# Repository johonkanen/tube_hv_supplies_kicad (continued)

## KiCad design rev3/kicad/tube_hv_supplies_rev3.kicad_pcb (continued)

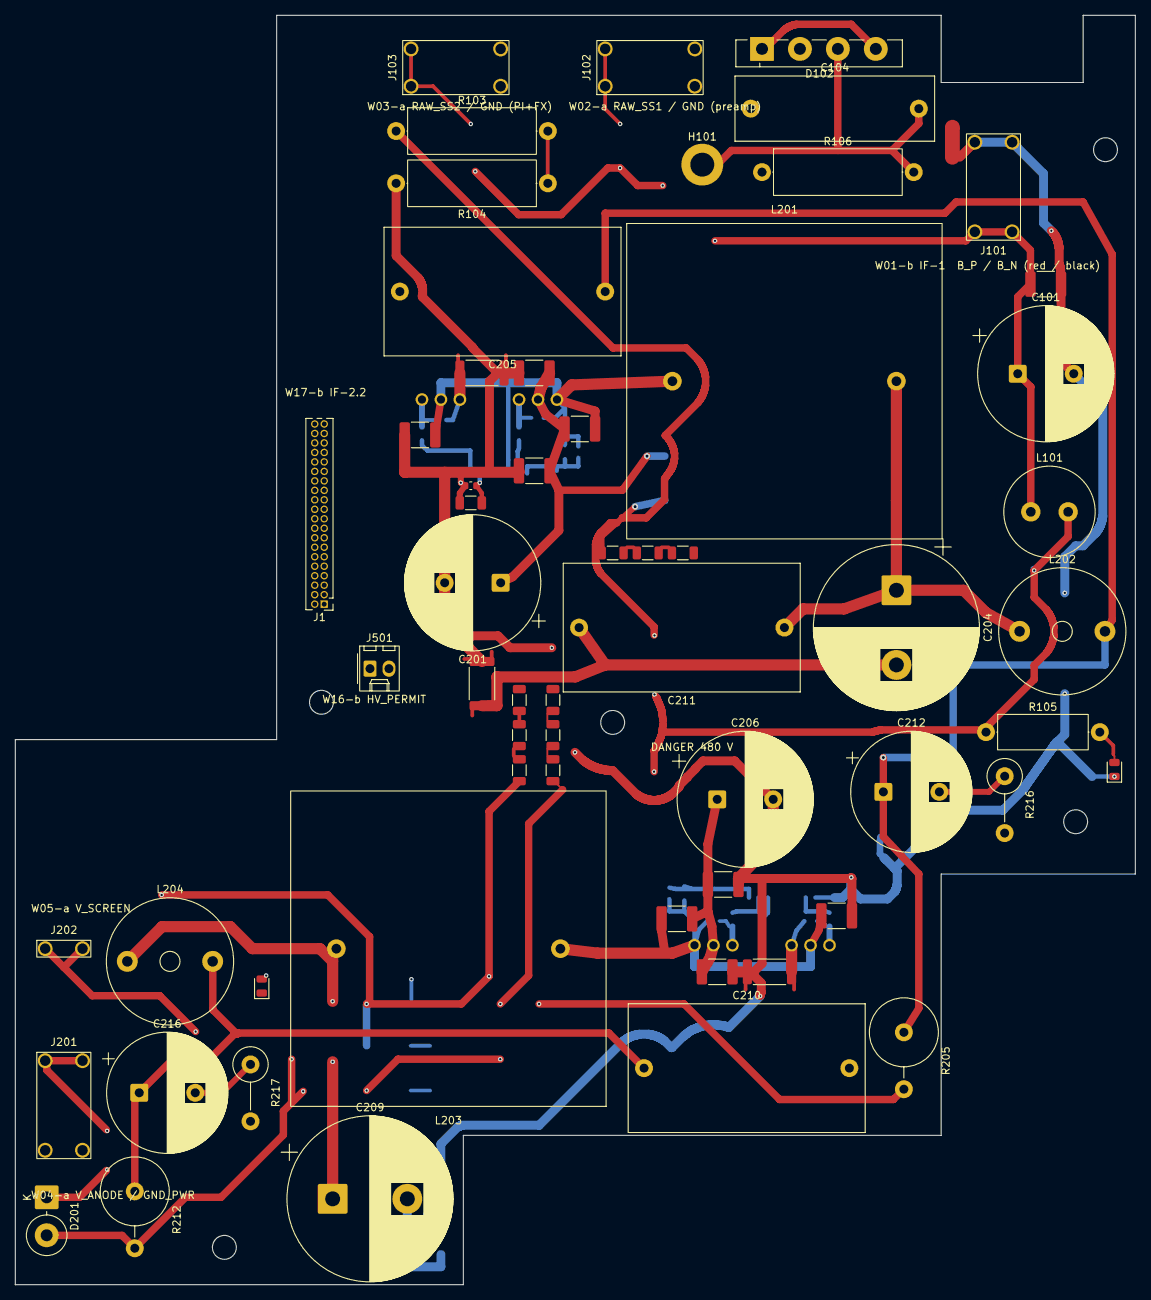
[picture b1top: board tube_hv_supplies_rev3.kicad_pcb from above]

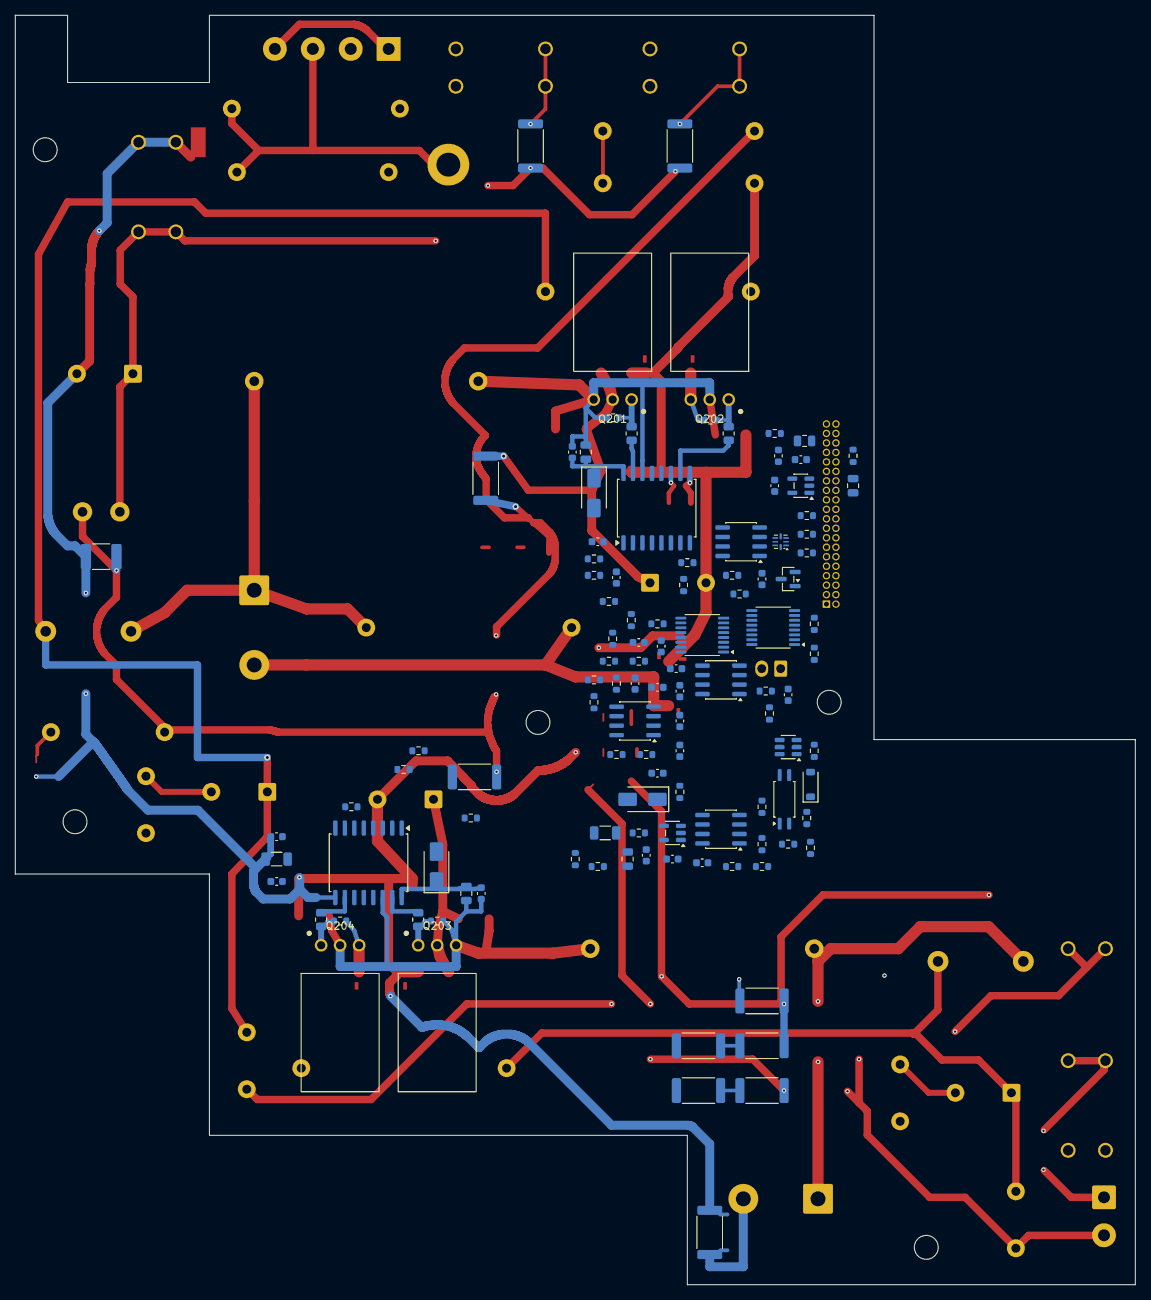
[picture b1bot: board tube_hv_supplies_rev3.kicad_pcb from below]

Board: 4 copper layers, 150.0 x 170.0 mm, 187 parts (115 on the bottom side), 108 nets.

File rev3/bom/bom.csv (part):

refs,qty,value,footprint,candidate_mpn,dnp,placeholder,note
C101 C201 C206,3,47u/500V 105C,Capacitor_THT:CP_Radial_D18.0mm_P7.50mm,,,,"radial D18, ripple rating at 70 C to check"
C102 C202 C207,3,100n/630V X7R 1812,Capacitor_SMD:C_1812_4532Metric,,,,
C103 C203 C208,3,1n/1kV C0G 1812,Capacitor_SMD:C_1812_4532Metric,,,,
C104,1,100n Y2 300VAC,Capacitor_THT:C_Rect_L26.5mm_W8.5mm_P22.50mm_MKS4,TDK B32023A3104M,,,"Y2 film, P22.5 (body width to check against the TDK drawing)"
C204 C209,2,100u/500V 105C 5000h snap-in,Capacitor_THT:CP_Radial_D22.0mm_P10.00mm_SnapIn,"Vishay MAL215919101E3 (PUL-SI, 22 x 40)",,,"TCM ripple 0.2-0.84 A rms at 40-150 kHz (sim/r2_filter.py); about 0.8 A at 120 Hz / 105 C rated, x1.4 at >= 10 kHz, more at 80 C: to confirm on the Vishay datasheet; alternative Rubycon 500VXT100MEFCSN22X25"
C205 C210 C211,3,4.7u/630V MKP DC-link,Capacitor_THT:C_Rect_L31.5mm_W17.0mm_P27.50mm_MKS4,TDK B32674D6475K,,,"C1 film, returned through the I_C shunt with the electrolytic: 0.2-0.76 A rms at 40-150 kHz (sim/r2); ripple rating to confirm on the TDK datasheet (DC-link series, ESR 7.5 mohm); C2 of the second stage (L2-C2 8.9 kHz); ESR 7.5 mohm; ripple current small (residue mV)"
C212 C216,2,22u/500V 105C,Capacitor_THT:CP_Radial_D16.0mm_P7.50mm,,,,damping leg of the second stage (with its ESR about 1.5 ohm in all); ripple small
C213 C217,2,"220p/1kV C0G 1812 (snubber, high side)",Capacitor_SMD:C_1812_4532Metric,,,,lossless ZVS snubber across the IGBT (sim/r1); at the device pins
C214 C218,2,"220p/1kV C0G 1812 (snubber, low side)",Capacitor_SMD:C_1812_4532Metric,,,,"lossless ZVS snubber across the IGBT, returned to PGND beside the shunt (keeps its charging current off the reading)"
C301 C303 C305 C308 C310 C312 C402 C404 C406 C408 C409 C410 C411 C414 C504 C505,16,100n,Capacitor_SMD:C_0603_1608Metric,,,,
C302 C309,2,1u/25V X7R,Capacitor_SMD:C_0805_2012Metric,,,,
C304 C311,2,10u/25V X7R,Capacitor_SMD:C_1206_3216Metric,,,,
C401 C403,2,100p C0G (tau 1.2 us),Capacitor_SMD:C_0603_1608Metric,,,,
C405,1,1n (tau 15 us),Capacitor_SMD:C_0603_1608Metric,,,,
C407 C413,2,1u X7R,Capacitor_SMD:C_0603_1608Metric,,,,
C412,1,"680p C0G (charge bucket, 22 ns)",Capacitor_SMD:C_0603_1608Metric,,,,
C415 C501,2,10u,Capacitor_SMD:C_0805_2012Metric,,,,
C416,1,10u X7R,Capacitor_SMD:C_0805_2012Metric,,,,
C502,1,10u/25V,Capacitor_SMD:C_1206_3216Metric,,,,
C503,1,10n,Capacitor_SMD:C_0603_1608Metric,,,,
D101,1,"red, 0.4 mA (HV PRESENT)",LED_SMD:LED_0805_2012Metric,,,,
D102,1,"GBU8J (8 A 600 V, + and - joined: anti-parallel pair)",Diode_THT:Diode_Bridge_Vishay_GBU,GBU8J,,,
D201,1,1N5408 (clamp: V_SCREEN <= V_ANODE + 0.7 V),Diode_THT:D_DO-201AD_P5.08mm_Vertical_CathodeUp,1N5408,,,
D202,1,"red, 0.4 mA (V_ANODE PRESENT)",LED_SMD:LED_0805_2012Metric,,,,
D301 D302,2,ES1J (600 V ultrafast),Diode_SMD:D_SMA,ES1J,,,
D501,1,SMAJ24CA,Diode_SMD:D_SMA,SMAJ24CA,,,
D502,1,1N4148W (reverse),Diode_SMD:D_SOD-123,1N4148W,,,
FB401,1,600R@100MHz 0603,Inductor_SMD:L_0603_1608Metric,,,,with C: the reference's input filter (LDO-derived 3V3 from the link)
H101,1,"CHASSIS standoff, plated (fault / RF network)",MountingHole:MountingHole_3.2mm_M3_DIN965_Pad,,,,new plate hole next to J101 (mechanical/floorplan.md)
H102 H103 H104 H105 H106,5,"M3, non-plated (no chassis contact)",MountingHole:MountingHole_3.2mm_M3,,,,"standoffs (fourth pass, mechanical/floorplan_chosen.md): (600.0, 98.0) (671.0, 48.0) (667.0, 138.0) (553.0, 195.0) (566.0, 122.0)"
J1,1,"CONTROL 40-pin IF-2.3 (W17-b, isolated on the control board)",Connector_PinHeader_1.27mm:PinHeader_2x20_P1.27mm_Vertical,Samtec SHF-120-01-L-D-TH,,,1.27 mm 2x20 shrouded THT header; the unused HV-to-card pads tied low
J101,2,"HV IN: B_P / B_N (W01-b, 4.8 mm tabs)",tube_hv_supplies_rev3:Blade_Tab_4.8mm_2x_P12mm,,,,"4.8 mm PCB blade tab(s), fully insulated receptacle; qty = tabs"
J102,2,RAW OUT 1 to preamp J501 (W02-a): RAW_SS1 / GND_PRE1,tube_hv_supplies_rev3:Blade_Tab_4.8mm_2x_P12mm,,,,"4.8 mm PCB blade tab(s), fully insulated receptacle; qty = tabs"
J103,2,RAW OUT 2 to PI + FX (W03-a): RAW_SS2 / GND_PRE2,tube_hv_supplies_rev3:Blade_Tab_4.8mm_2x_P12mm,,,,"4.8 mm PCB blade tab(s), fully insulated receptacle; qty = tabs"
J201,2,"V_ANODE / GND_PWR (W04-a, 4.8 mm tabs)",tube_hv_supplies_rev3:Blade_Tab_4.8mm_2x_P12mm,,,,"4.8 mm PCB blade tab(s), fully insulated receptacle; qty = tabs"
J202,1,"V_SCREEN (W05-a, 4.8 mm tab)",tube_hv_supplies_rev3:Blade_Tab_4.8mm_1x,,,,"4.8 mm PCB blade tab(s), fully insulated receptacle; qty = tabs"
J501,1,"HV_PERMIT +/- (W16-b, Lock-2.54, twisted pair)",Connector_Molex:Molex_KK-254_AE-6410-02A_1x02_P2.54mm_Vertical,Molex 22-27-2021,,,
L101,1,33uH 2A,Inductor_THT:L_Radial_D12.0mm_P5.00mm_Fastron_11P,,,,"33 uH, >= 2 A, radial D12"
L201,1,"220uH ETD39 N97, 50t litz 0.8mm2, gap ~1.8mm (Isat >= 10A, DCR ~0.1R hot)",tube_hv_supplies_rev3:L_ETD39_2pin_custom,TDK B66363G0000X197 (N97) core set + ETD39 bobbin,,,custom-wound; litz 0.1 mm strands; gap split or winding kept 3 mm from the gap (fringing); 600 V winding-core insulation; pin positions to the chosen bobbin
L202 L204,2,68uH >= 2A,Inductor_THT:L_Radial_D16.8mm_P11.43mm_Vishay_IHB-1,Vishay IHB-1 68 uH (current rating to confirm >= 2 A),,,"second stage: carries the DC output current and the audio current, almost no ripple"
L203,1,"470uH ETD39 N97, 64t litz 0.5mm2, gap ~1.4mm (Isat >= 6A, DCR ~0.2R hot)",tube_hv_supplies_rev3:L_ETD39_2pin_custom,TDK B66363G0000X197 (N97) core set + ETD39 bobbin,,,custom-wound; litz 0.1 mm strands; gap split or winding kept 3 mm from the gap (fringing); 600 V winding-core insulation; pin positions to the chosen bobbin
NT101,1,STAR POINT (power star),NetTie:NetTie-2_SMD_Pad2.0mm,,,,
NT401,1,Kelvin tap IC1 (at the shunt),NetTie:NetTie-2_SMD_Pad0.5mm,,,,
NT402 NT404 NT406 NT408,4,Kelvin tap PGND (at the shunt),NetTie:NetTie-2_SMD_Pad0.5mm,,,,
NT403,1,Kelvin tap IS1 (at the shunt),NetTie:NetTie-2_SMD_Pad0.5mm,,,,
NT405,1,Kelvin tap IC2 (at the shunt),NetTie:NetTie-2_SMD_Pad0.5mm,,,,
NT407,1,Kelvin tap IS2 (at the shunt),NetTie:NetTie-2_SMD_Pad0.5mm,,,,
NT501,1,GND to PGND at the shunts (Kelvin),NetTie:NetTie-2_SMD_Pad0.5mm,,,,
Q201 Q202 Q203 Q204,4,IKP08N65F5,tube_hv_supplies_rev3:TO-220-3_Horizontal_TabUp_Bar,IKP08N65F5XKSA1,,,"lies on the chassis plate: 6 mm aluminium bar, 1.5 mm Al2O3 washer, PEEK shoulder bush, M3 countersunk from the plate's top with a nut on the tab (fitted before the board); leads bent down 90 deg about 5 mm into the board (STATUS fourth pass). Collector tab live: raw rail (high side); lies on the chassis plate: 6 mm aluminium bar, 1.5 mm Al2O3 washer, PEEK shoulder bush, M3 countersunk from the plate's top with a nut on the tab (fitted before the board); leads bent down 90 deg about 5 mm into the board (STATUS fourth pass). Collector tab live: switch node (low side)"
R101 R102,2,0R jumper 2512 (link),Resistor_SMD:R_2512_6332Metric,,,,"link (interfaces.md 4.2), plate side; the fusible-resistor option of the 0617 footprint is dropped (board area, fourth pass)"
R103 R104,2,75k 2W MOX,Resistor_THT:R_Axial_DIN0617_L17.0mm_D6.0mm_P20.32mm_Horizontal,,,,0.62 W each at 430 V
R105,1,1M 1W HV (VR37 class),Resistor_THT:R_Axial_DIN0414_L11.9mm_D4.5mm_P15.24mm_Horizontal,,,,
R106,1,100 2W,Resistor_THT:R_Axial_DIN0617_L17.0mm_D6.0mm_P20.32mm_Horizontal,,,,
R201 R208,2,0R jumper 2512 (bridge input link),Resistor_SMD:R_2512_6332Metric,,,,proposal N7: no fuse (PSU short-circuit protection + 3.0 A trips); plate side (fourth pass)
R202 R203 R209 R210,4,50m 1W 2512 metal strip (Kelvin),Resistor_SMD:R_2512_6332Metric,Vishay WSL2512R0500FEA,,,metal element: M20 pulses up to 220 A / 0.29 J in 0.2 ms on the I_C shunt (pulse rating to confirm)
R205,1,"1.0 5W fusible, pulse (ULW5)",Resistor_THT:R_Axial_DIN0918_L18.0mm_D9.0mm_P7.62mm_Vertical,TT Welwyn ULW5-1R0J (ordering suffix to confirm),,,"M20: a hard short or external arc puts 5.8-6.7 J into it in 0.2 ms; ULW5 short-pulse capacity ~19 J (1R0) / ~13 J (2R2), 500 V isolation (ULW2: 2.5 J, 250 V)"
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
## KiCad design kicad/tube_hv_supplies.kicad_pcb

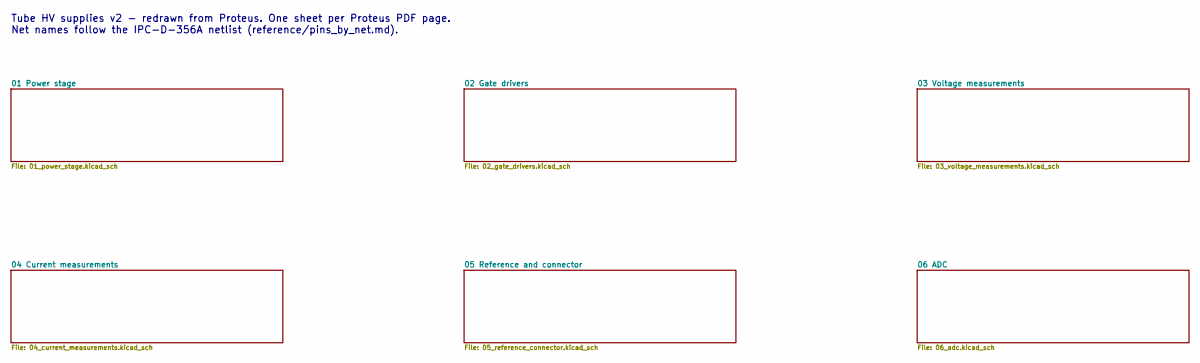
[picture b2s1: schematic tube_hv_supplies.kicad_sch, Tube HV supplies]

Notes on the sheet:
Tube HV supplies v2 - redrawn from Proteus. One sheet per Proteus PDF page. Net names follow the IPC-D-356A netlist (reference/pins_by_net.md).

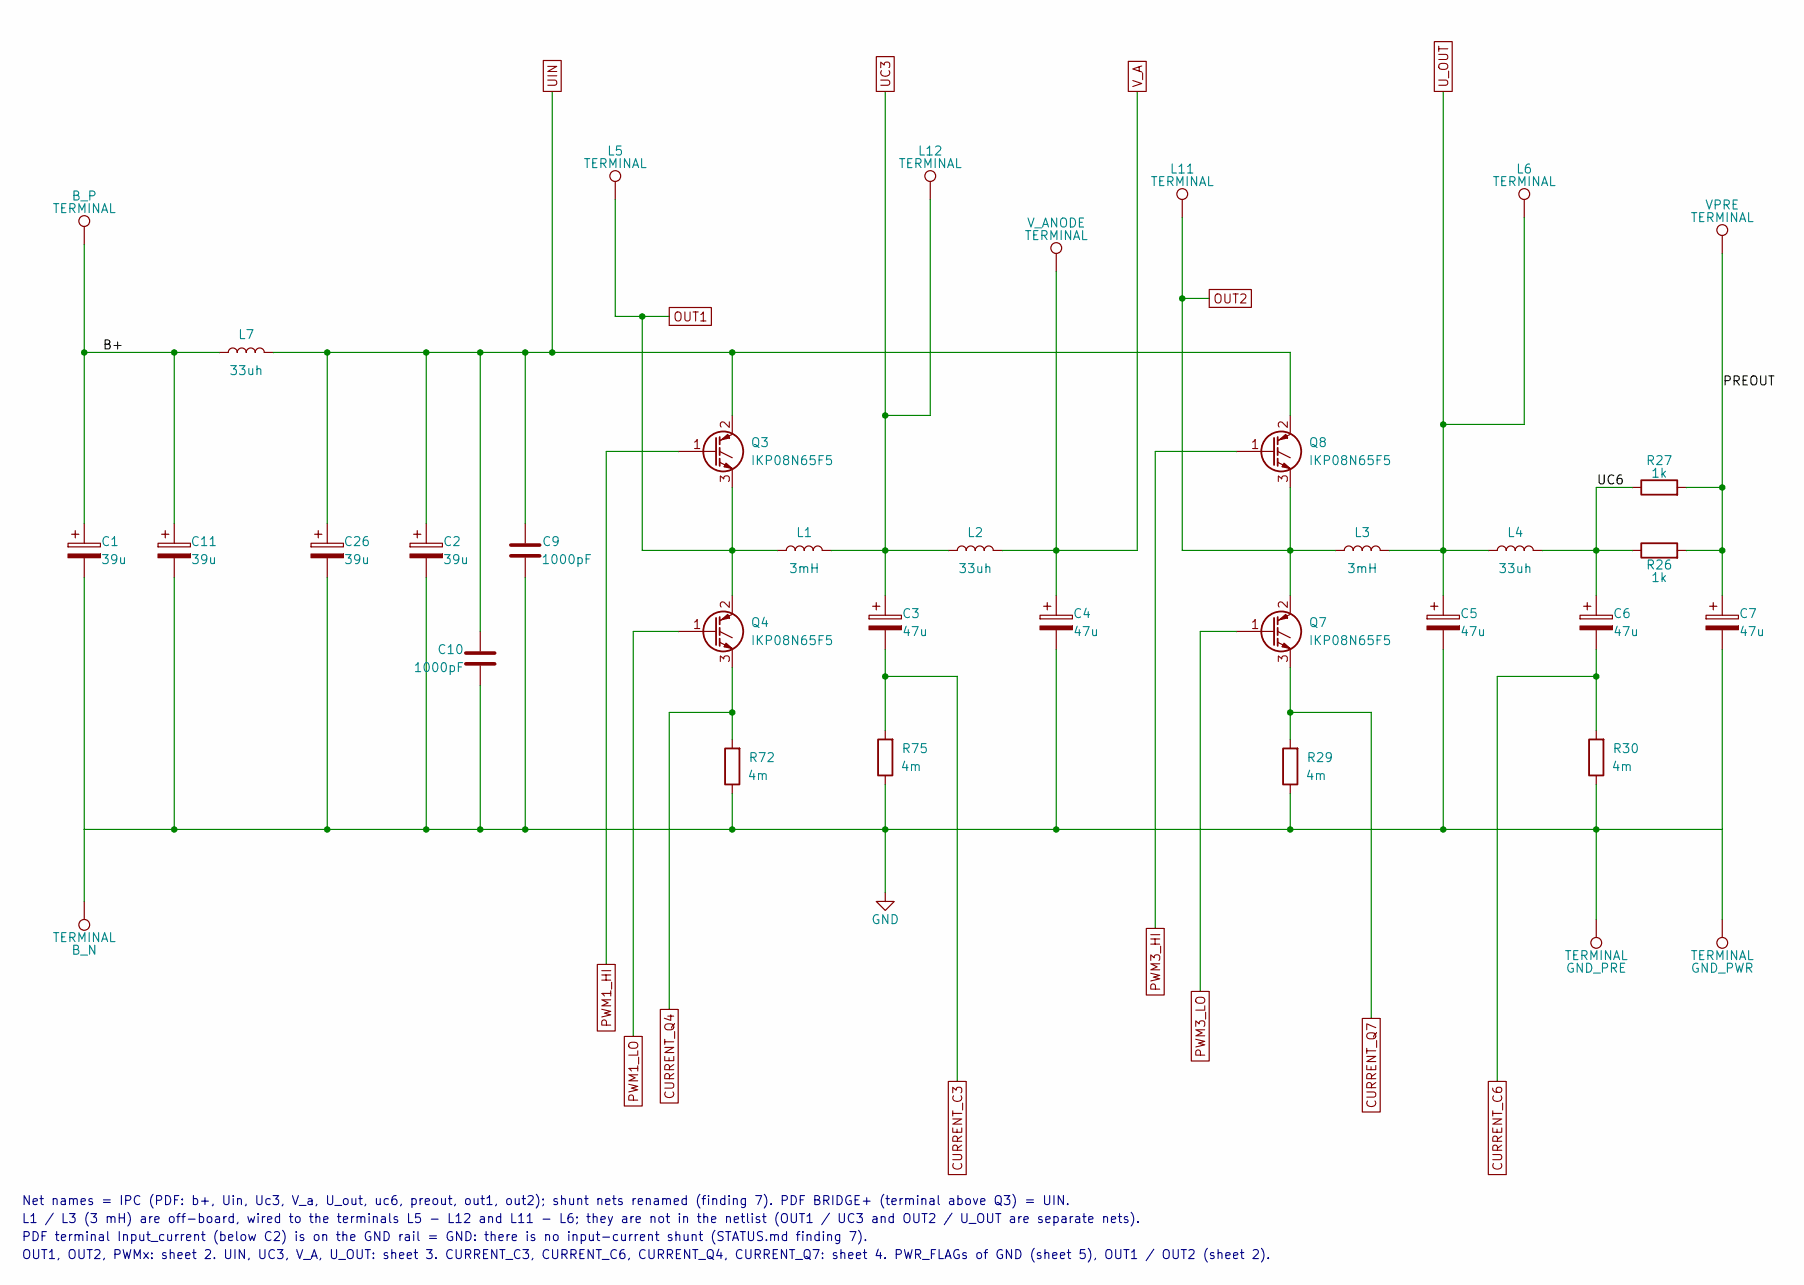
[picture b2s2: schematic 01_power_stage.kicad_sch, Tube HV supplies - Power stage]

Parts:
B_N: TERMINAL; Terminal_2x1_P5.00mm_D2.0mm_Drill1.4mm
B_P: TERMINAL; Terminal_2x1_P5.00mm_D2.0mm_Drill1.4mm
C1, C2, C11, C26: 39u; CP_Radial_D10.0mm_P5.00mm
C3, C4, C5, C6, C7: 47u; CP_Radial_D10.0mm_P5.00mm
C9, C10: 1000pF; C_2220_5750Metric_Pad1.97x5.40mm_HandSolder
GND_PRE: TERMINAL; Terminal_2x1_P5.00mm_D2.0mm_Drill1.4mm
GND_PWR: TERMINAL; Terminal_2x1_P5.00mm_D2.0mm_Drill1.4mm
L1, L3: 3mH
L2, L4, L7: 33uh; L_Bourns_SRP1038C_10.0x10.0mm_Proteus
L5, L6, L11, L12: TERMINAL; Terminal_1x1_D2.54mm_Drill1.524mm
Q3, Q4, Q7, Q8: IKP08N65F5; TO-220-3_Vertical_ProteusPads
R26, R27: 1k; R_1206_3216Metric_Pad1.30x1.75mm_HandSolder
R29, R30, R72, R75: 4m; R_0508_1220Metric_KRL2012
VPRE: TERMINAL; Terminal_2x1_P5.00mm_D2.0mm_Drill1.4mm
V_ANODE: TERMINAL; Terminal_2x1_P5.00mm_D2.0mm_Drill1.4mm

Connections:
/01 Power stage/B+: B_P.1, C1.1, C11.1, L7.1
/01 Power stage/PREOUT: C7.1, R26.2, R27.2, VPRE.1
/01 Power stage/UC6: C6.1, L4.2, R26.1, R27.1
CURRENT_C3: C3.2, R75.2; also elsewhere on the board
CURRENT_C6: C6.2, R30.2; also elsewhere on the board
CURRENT_Q4: Q4.3 (E), R72.2; also elsewhere on the board
CURRENT_Q7: Q7.3 (E), R29.2; also elsewhere on the board
GND: B_N.1, C1.2, C2.2, C4.2, C5.2, C7.2, C9.2, C10.2, C11.2, C26.2, GND_PRE.1, GND_PWR.1, R29.1, R30.1, R72.1, R75.1; also elsewhere on the board
OUT1: L1.1, L5.1, Q3.3 (E), Q4.2 (C); also elsewhere on the board
OUT2: L3.1, L11.1, Q7.2 (C), Q8.3 (E); also elsewhere on the board
PWM1_HI: Q3.1 (G); also elsewhere on the board
PWM1_LO: Q4.1 (G); also elsewhere on the board
PWM3_HI: Q8.1 (G); also elsewhere on the board
PWM3_LO: Q7.1 (G); also elsewhere on the board
UC3: C3.1, L1.2, L2.1, L12.1; also elsewhere on the board
UIN: C2.1, C9.1, C10.1, C26.1, L7.2, Q3.2 (C), Q8.2 (C); also elsewhere on the board
U_OUT: C5.1, L3.2, L4.1, L6.1; also elsewhere on the board
V_A: C4.1, L2.2, V_ANODE.1; also elsewhere on the board

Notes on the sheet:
Net names = IPC (PDF: b+, Uin, Uc3, V_a, U_out, uc6, preout, out1, out2); shunt nets renamed (finding 7). PDF BRIDGE+ (terminal above Q3) = UIN.
L1 / L3 (3 mH) are off-board, wired to the terminals L5 - L12 and L11 - L6; they are not in the netlist (OUT1 / UC3 and OUT2 / U_OUT are separate nets).
PDF terminal Input_current (below C2) is on the GND rail = GND: there is no input-current shunt (STATUS.md finding 7).
OUT1, OUT2, PWMx: sheet 2. UIN, UC3, V_A, U_OUT: sheet 3. CURRENT_C3, CURRENT_C6, CURRENT_Q4, CURRENT_Q7: sheet 4. PWR_FLAGs of GND (sheet 5), OUT1 / OUT2 (sheet 2).

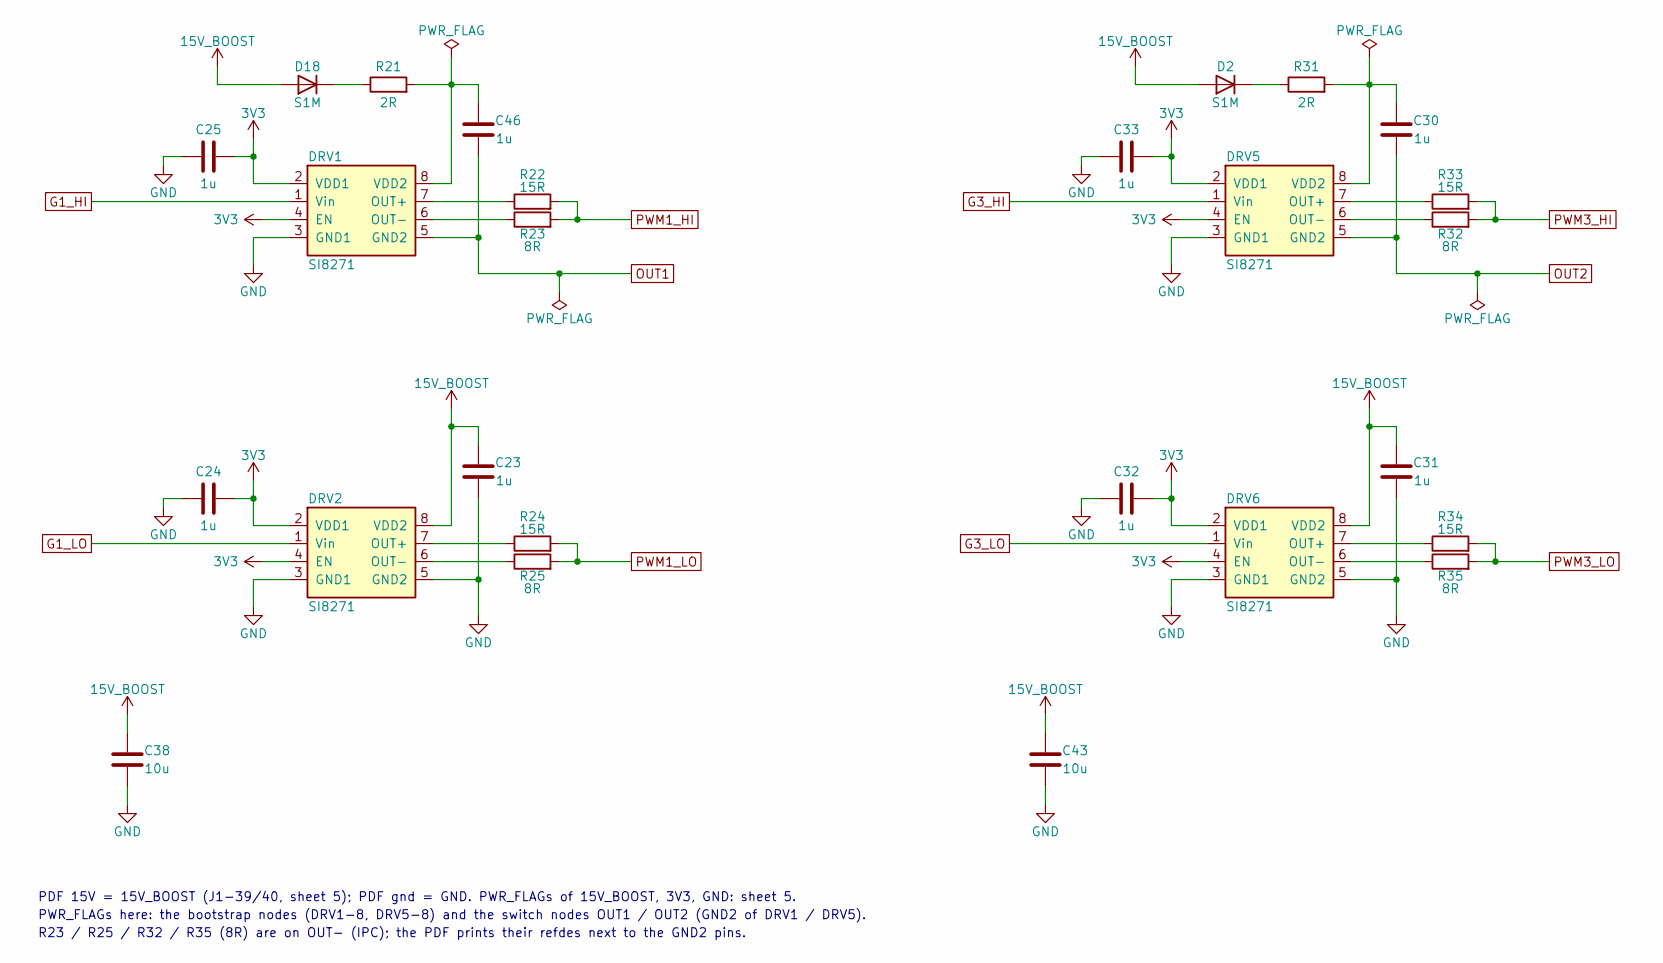
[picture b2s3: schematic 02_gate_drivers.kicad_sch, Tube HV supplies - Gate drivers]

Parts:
C23, C30, C31, C46: 1u; C_1206_3216Metric_Pad1.33x1.80mm_HandSolder
C24, C25, C32, C33: 1u; C_0603_1608Metric_Pad1.08x0.95mm_HandSolder
C38, C43: 10u; C_1206_3216Metric_Pad1.33x1.80mm_HandSolder
D2, D18: S1M; D_SMA_AC
DRV1, DRV2: SI8271; SOIC-8_3.9x4.9mm_P1.27mm_Proteus
DRV5, DRV6: SI8271; SOIC-8_3.9x4.9mm_P1.27mm_Proteus_ProteusPads
R21, R31: 2R; R_1206_3216Metric
R22, R24, R33, R34: 15R; R_1206_3216Metric_Pad1.30x1.75mm_HandSolder
R23, R25, R32, R35: 8R; R_1206_3216Metric_Pad1.30x1.75mm_HandSolder

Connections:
3V3: C24.2, C25.2, C32.2, C33.2, DRV1.2 (VDD1), DRV1.4 (EN), DRV2.2 (VDD1), DRV2.4 (EN), DRV5.2 (VDD1), DRV5.4 (EN), DRV6.2 (VDD1), DRV6.4 (EN); also elsewhere on the board
15V_BOOST: C23.1, C31.1, C38.1, C43.1, D2.A, D18.A, DRV2.8 (VDD2), DRV6.8 (VDD2); also elsewhere on the board
G1_HI: DRV1.1 (Vin); also elsewhere on the board
G1_LO: DRV2.1 (Vin); also elsewhere on the board
G3_HI: DRV5.1 (Vin); also elsewhere on the board
G3_LO: DRV6.1 (Vin); also elsewhere on the board
GND: C23.2, C24.1, C25.1, C31.2, C32.1, C33.1, C38.2, C43.2, DRV1.3 (GND1), DRV2.3 (GND1), DRV2.5 (GND2), DRV5.3 (GND1), DRV6.3 (GND1), DRV6.5 (GND2); also elsewhere on the board
unnamed: D2.C (K), R31.1
unnamed: D18.C (K), R21.1
unnamed: DRV1.7 (OUT+), R22.1
unnamed: DRV1.6 (OUT-), R23.1
unnamed: C46.2, DRV1.8 (VDD2), R21.2
unnamed: DRV2.7 (OUT+), R24.1
unnamed: DRV2.6 (OUT-), R25.1
unnamed: DRV5.7 (OUT+), R33.1
unnamed: DRV5.6 (OUT-), R32.1
unnamed: C30.2, DRV5.8 (VDD2), R31.2
unnamed: DRV6.7 (OUT+), R34.1
unnamed: DRV6.6 (OUT-), R35.1
OUT1: C46.1, DRV1.5 (GND2); also elsewhere on the board
OUT2: C30.1, DRV5.5 (GND2); also elsewhere on the board
PWM1_HI: R22.2, R23.2; also elsewhere on the board
PWM1_LO: R24.2, R25.2; also elsewhere on the board
PWM3_HI: R32.2, R33.2; also elsewhere on the board
PWM3_LO: R34.2, R35.2; also elsewhere on the board

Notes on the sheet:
PDF 15V = 15V_BOOST (J1-39/40, sheet 5); PDF gnd = GND. PWR_FLAGs of 15V_BOOST, 3V3, GND: sheet 5.
PWR_FLAGs here: the bootstrap nodes (DRV1-8, DRV5-8) and the switch nodes OUT1 / OUT2 (GND2 of DRV1 / DRV5).
R23 / R25 / R32 / R35 (8R) are on OUT- (IPC); the PDF prints their refdes next to the GND2 pins.

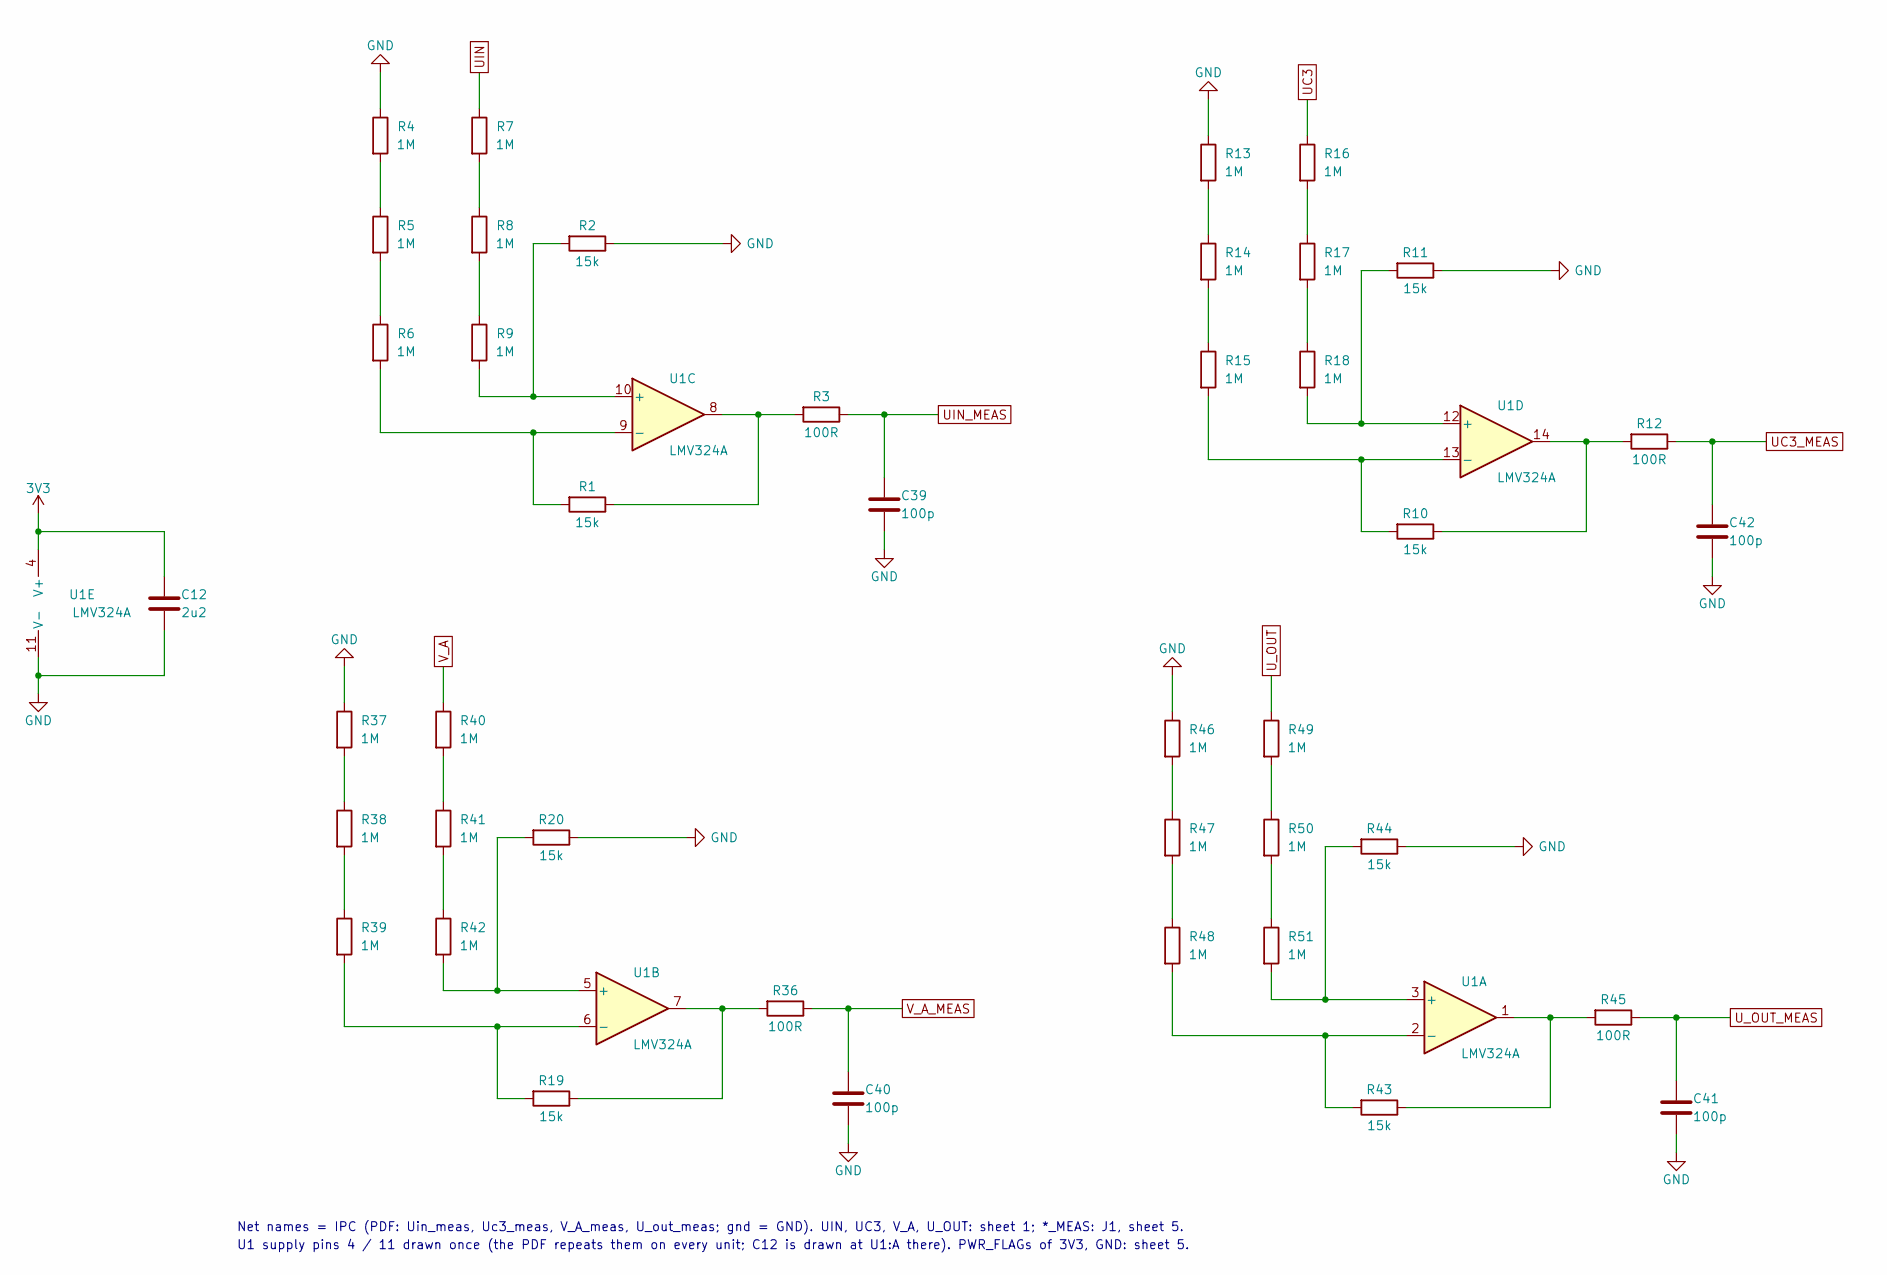
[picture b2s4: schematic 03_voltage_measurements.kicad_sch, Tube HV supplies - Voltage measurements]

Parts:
C12: 2u2; C_0603_1608Metric
C39, C40, C41, C42: 100p; C_0603_1608Metric
R1, R2, R10, R11, R19, R20, R43, R44: 15k; R_0402_1005Metric_Proteus0.91
R3, R12, R36, R45: 100R; R_0603_1608Metric
R4, R5, R6, R7, R8, R9, R13, R14, R15, R16, R17, R18, R37, R38, R39, R40, R41, R42, R46, R47, R48, R49, R50, R51: 1M; R_1206_3216Metric_Pad1.30x1.75mm_HandSolder
U1: LMV324A; TSSOP-14_4.4x5mm_P0.65mm_Proteus_ProteusPads

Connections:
3V3: C12.1, U1.4 (V+); also elsewhere on the board
GND: C12.2, C39.2, C40.2, C41.2, C42.2, R2.1, R4.1, R11.1, R13.1, R20.1, R37.1, R44.1, R46.1, U1.11 (V-); also elsewhere on the board
unnamed: R1.1, R3.2, U1.8
unnamed: R4.2, R5.1
unnamed: R5.2, R6.1
unnamed: R7.2, R8.1
unnamed: R8.2, R9.1
unnamed: R10.1, R12.2, U1.14
unnamed: R13.2, R14.1
unnamed: R14.2, R15.1
unnamed: R16.2, R17.1
unnamed: R17.2, R18.1
unnamed: R19.1, R36.2, U1.7
unnamed: R37.2, R38.1
unnamed: R38.2, R39.1
unnamed: R40.2, R41.1
unnamed: R41.2, R42.1
unnamed: R43.1, R45.2, U1.1
unnamed: R46.2, R47.1
unnamed: R47.2, R48.1
unnamed: R49.2, R50.1
unnamed: R50.2, R51.1
unnamed: R44.2, R51.2, U1.3 (+)
unnamed: R43.2, R48.2, U1.2 (-)
unnamed: R20.2, R42.2, U1.5 (+)
unnamed: R19.2, R39.2, U1.6 (-)
unnamed: R2.2, R9.2, U1.10 (+)
unnamed: R1.2, R6.2, U1.9 (-)
unnamed: R11.2, R18.2, U1.12 (+)
unnamed: R10.2, R15.2, U1.13 (-)
UC3: R16.1; also elsewhere on the board
UC3_MEAS: C42.1, R12.1; also elsewhere on the board
UIN: R7.1; also elsewhere on the board
UIN_MEAS: C39.1, R3.1; also elsewhere on the board
U_OUT: R49.1; also elsewhere on the board
U_OUT_MEAS: C41.1, R45.1; also elsewhere on the board
V_A: R40.1; also elsewhere on the board
V_A_MEAS: C40.1, R36.1; also elsewhere on the board

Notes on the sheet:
Net names = IPC (PDF: Uin_meas, Uc3_meas, V_A_meas, U_out_meas; gnd = GND). UIN, UC3, V_A, U_OUT: sheet 1; *_MEAS: J1, sheet 5.
U1 supply pins 4 / 11 drawn once (the PDF repeats them on every unit; C12 is drawn at U1:A there). PWR_FLAGs of 3V3, GND: sheet 5.

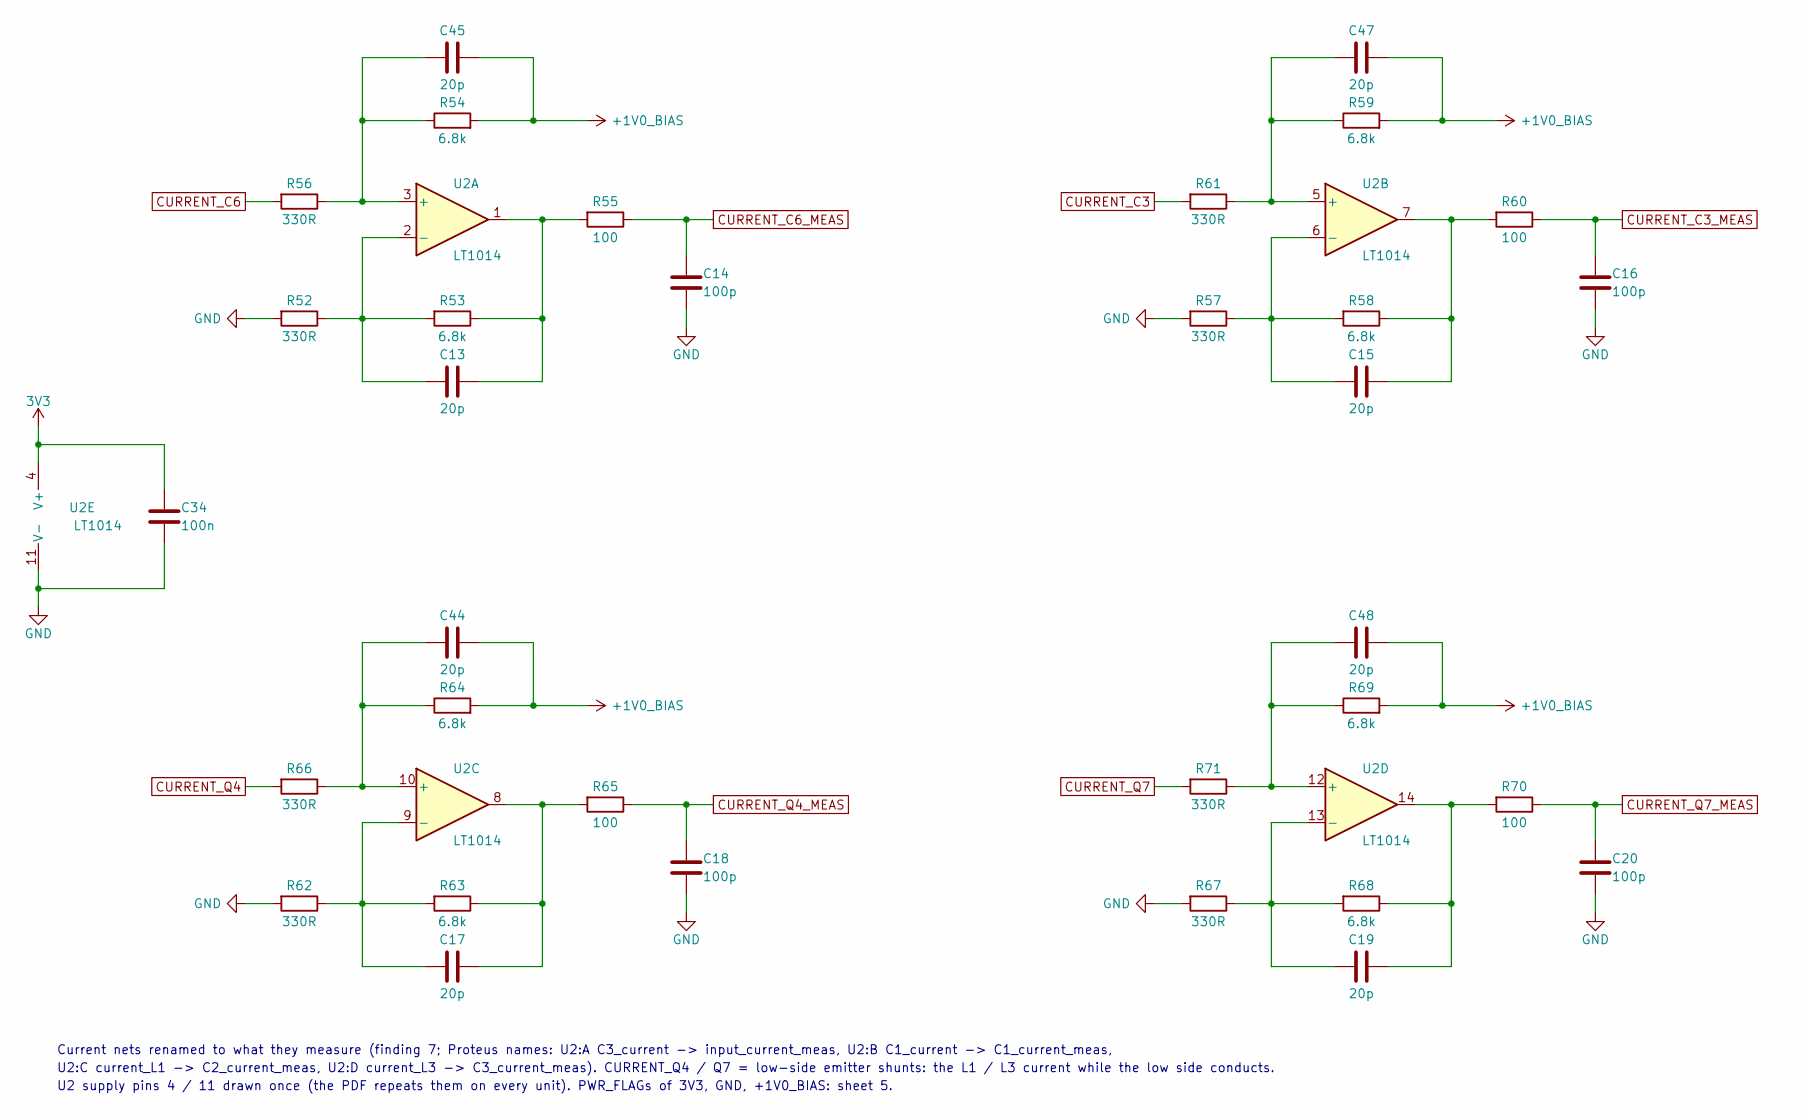
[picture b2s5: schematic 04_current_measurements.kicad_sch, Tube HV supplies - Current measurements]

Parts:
C13, C15, C17, C19, C44, C45, C47, C48: 20p; C_0603_1608Metric
C14, C16, C18, C20: 100p; C_0603_1608Metric
C34: 100n; C_0603_1608Metric
R52, R56, R57, R61, R62, R66, R67, R71: 330R; R_0402_1005Metric_Proteus0.91
R53, R54, R58, R59, R63, R64, R68, R69: 6.8k; R_0402_1005Metric_Proteus0.91
R55, R60, R65, R70: 100; R_0402_1005Metric_Proteus0.91
U2: LT1014; TSSOP-14_4.4x5mm_P0.65mm_Proteus_ProteusPads

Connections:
3V3: C34.2, U2.4 (V+); also elsewhere on the board
+1V0_BIAS: C44.1, C45.1, C47.1, C48.1, R54.2, R59.2, R64.2, R69.2; also elsewhere on the board
CURRENT_C3: R61.2; also elsewhere on the board
CURRENT_C3_MEAS: C16.1, R60.1; also elsewhere on the board
CURRENT_C6: R56.2; also elsewhere on the board
CURRENT_C6_MEAS: C14.1, R55.1; also elsewhere on the board
CURRENT_Q4: R66.2; also elsewhere on the board
CURRENT_Q4_MEAS: C18.1, R65.1; also elsewhere on the board
CURRENT_Q7: R71.2; also elsewhere on the board
CURRENT_Q7_MEAS: C20.1, R70.1; also elsewhere on the board
GND: C14.2, C16.2, C18.2, C20.2, C34.1, R52.2, R57.2, R62.2, R67.2, U2.11 (V-); also elsewhere on the board
unnamed: C13.1, R53.1, R55.2, U2.1
unnamed: C15.1, R58.1, R60.2, U2.7
unnamed: C17.1, R63.1, R65.2, U2.8
unnamed: C19.1, R68.1, R70.2, U2.14
unnamed: C45.2, R54.1, R56.1, U2.3 (+)
unnamed: C13.2, R52.1, R53.2, U2.2 (-)
unnamed: C47.2, R59.1, R61.1, U2.5 (+)
unnamed: C15.2, R57.1, R58.2, U2.6 (-)
unnamed: C44.2, R64.1, R66.1, U2.10 (+)
unnamed: C17.2, R62.1, R63.2, U2.9 (-)
unnamed: C48.2, R69.1, R71.1, U2.12 (+)
unnamed: C19.2, R67.1, R68.2, U2.13 (-)

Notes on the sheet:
Current nets renamed to what they measure (finding 7; Proteus names: U2:A C3_current -> input_current_meas, U2:B C1_current -> C1_current_meas,
U2:C current_L1 -> C2_current_meas, U2:D current_L3 -> C3_current_meas). CURRENT_Q4 / Q7 = low-side emitter shunts: the L1 / L3 current while the low side conducts.
U2 supply pins 4 / 11 drawn once (the PDF repeats them on every unit). PWR_FLAGs of 3V3, GND, +1V0_BIAS: sheet 5.
